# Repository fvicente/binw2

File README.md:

# binw2
Binary Wrist Watch with ATtiny13

# Debugging
simulavr -g -d attiny45
avr-gdb
(gdb) target remote localhost:1212
(gdb) file /Users/fvicente/workspace/alfersoft.com.ar-repos/binw2/src/binw2.o
(gdb) load
(gdb) step

# Preparing pysimulavr
brew install swig
cd simulavr/src/python
sudo python2.6 setup.py install

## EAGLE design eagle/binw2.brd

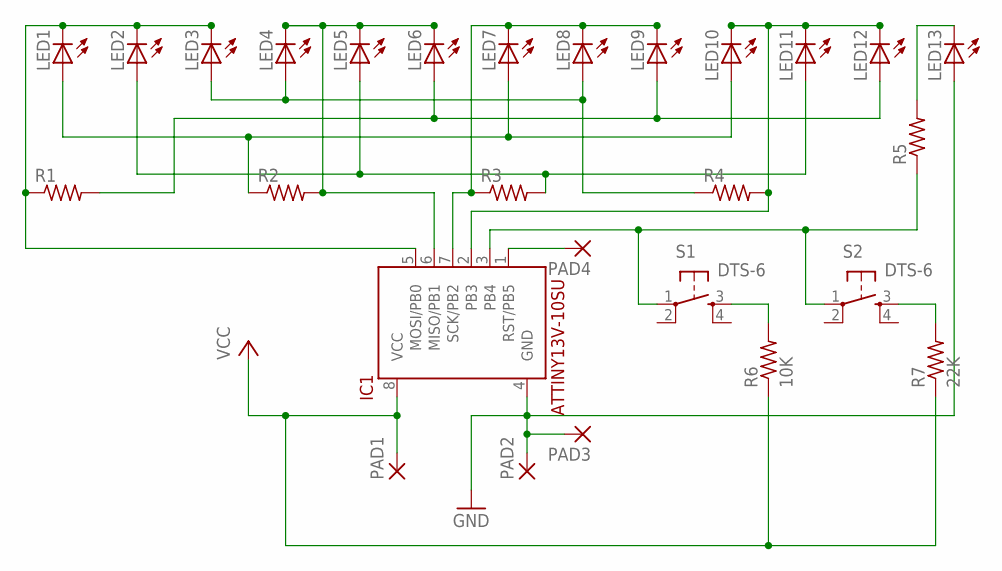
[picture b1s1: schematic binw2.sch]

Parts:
IC1: ATTINY13V-10SU; SOIC8
LED1, LED2, LED3, LED4, LED5, LED6, LED7, LED8, LED9, LED10, LED11, LED12, LED13: LEDCHIP-LED0805; CHIP-LED0805
PAD1, PAD2, PAD3, PAD4: 1,6/0,8
R1, R2, R3, R4, R5: R-US_R0805; R0805
R6: 10K; R0805
R7: 22K; R0805
S1, S2: DTS-6

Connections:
GND: IC1.4 (GND), LED13.A, PAD2.1, PAD3.1
unnamed: IC1.1 (RST/PB5), PAD4.1
unnamed: R7.2, S2.3
unnamed: LED13.C, R5.2
unnamed: IC1.3 (PB4), R5.1, S1.1, S2.1
unnamed: IC1.5 (MOSI/PB0), LED1.C, LED2.C, LED3.C, R1.1
unnamed: LED1.A, LED7.A, LED10.A, R2.1
unnamed: IC1.6 (MISO/PB1), LED4.C, LED5.C, LED6.C, R2.2
unnamed: IC1.7 (SCK/PB2), LED7.C, LED8.C, LED9.C, R3.1
unnamed: IC1.2 (PB3), LED10.C, LED11.C, LED12.C, R4.2
unnamed: LED3.A, LED4.A, LED8.A, R4.1
unnamed: R6.2, S1.3
unnamed: LED2.A, LED5.A, LED11.A, R3.2
unnamed: LED6.A, LED9.A, LED12.A, R1.2
VCC: IC1.8 (VCC), PAD1.1, R6.1, R7.1

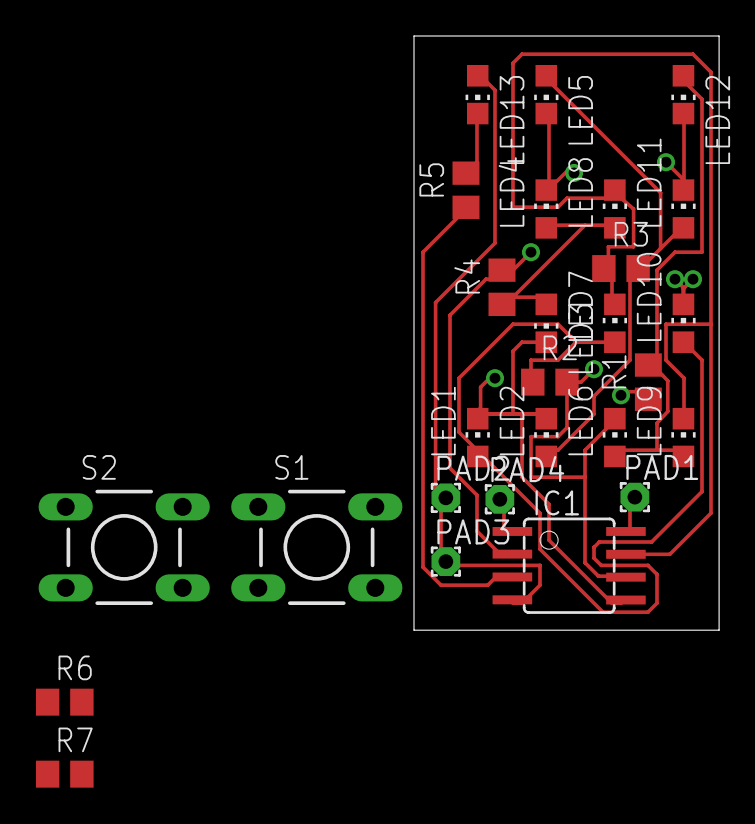
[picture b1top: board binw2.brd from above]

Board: 2 copper layers, 16.9 x 33.0 mm, 27 parts (0 on the bottom side), 15 nets.

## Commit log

2016-06-08 Accelerated version for test
2016-10-07 Starting program mode
2016-10-23 Givin' a try to simavr
2016-10-25 Added simulation leds
2016-11-03 Removed BCD conversion, incrementing directly as BCD. No charlieplexing table thus no lpm
2016-11-03 Adjusting simulator
2016-11-04 Added AM/PM led
2016-11-04 Code improvement
2018-03-05 I don't even know :)
